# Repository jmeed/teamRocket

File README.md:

teamRocket
==========

Team Rocket Blasting off again!

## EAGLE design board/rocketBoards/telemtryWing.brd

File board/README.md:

Get Eagle 6.6 (not 7.1)

windows:
http://web.cadsoft.de/ftp/eagle/program/6.6/eagle-win-6.6.0.exe

linux:
http://web.cadsoft.de/ftp/eagle/program/6.6/eagle-lin-6.6.0.run

mac:
http://web.cadsoft.de/ftp/eagle/program/6.6/eagle-mac-6.6.0.zip

License Key for eagle 6.*: ficbbfxmxv

The license file is in this directory

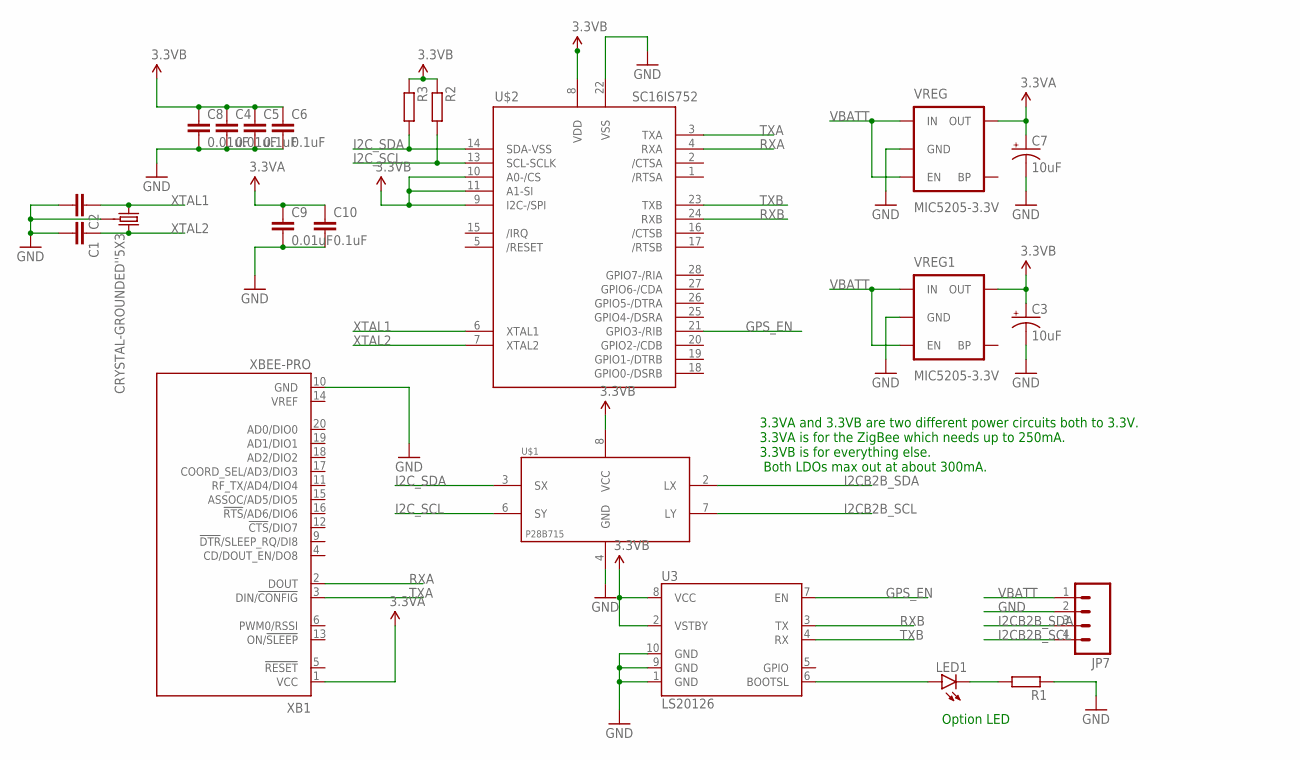
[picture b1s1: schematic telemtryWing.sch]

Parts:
C1, C2: C0603
C3, C7: 10uF; EIA3216
C4, C8, C9: 0.01uF; C0603
C5, C6, C10: 0.1uF; C0603
JP7: M04JST; 1X04-1.5MM_JST
LED1: LED0603; LED-0603
R1, R2, R3: R0603
U3: LS20126
U$1: P82B715; SO8
U$2: SC16IS752; TSSOP28
U$3: CRYSTAL-GROUNDED''5X3; CRYSTAL-SMD-5X3
VREG, VREG1: MIC5205-3.3V; SOT23-5
XB1: XBEE-PRO

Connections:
3.3V: C3.A (+), C4.1, C5.1, C6.1, C8.1, R2.1, R3.1, U3.2 (VSTBY), U3.8 (VCC), U$1.8 (VCC), U$2.8 (VDD), U$2.9 (I2C-/SPI), U$2.10 (A0-/CS), U$2.11 (A1-SI), VREG1.5 (OUT)
GND: C1.2, C2.2, C3.C (-), C4.2, C5.2, C6.2, C7.C (-), C8.2, C9.2, C10.2, JP7.2, R1.1, U3.1 (GND), U3.9 (GND), U3.10 (GND), U$1.4 (GND), U$2.22 (VSS), U$3.2 (3), U$3.4 (3), VREG.2 (GND), VREG1.2 (GND), XB1.10 (GND)
GPS_EN: U3.7 (EN), U$2.21 (GPIO3-/RIB)
I2CB2B_SCL: JP7.4, U$1.7 (LY)
I2CB2B_SDA: JP7.3, U$1.2 (LX)
I2C_SCL: R2.2, U$1.6 (SY), U$2.13 (SCL-SCLK)
I2C_SDA: R3.2, U$1.3 (SX), U$2.14 (SDA-VSS)
unnamed: LED1.C, R1.2
unnamed: LED1.A, U3.6 (BOOTSL)
RXA: U$2.4 (RXA), XB1.2 (DOUT)
RXB: U3.3 (TX), U$2.24 (RXB)
TXA: U$2.3 (TXA), XB1.3 (DIN/!CONFIG)
TXB: U3.4 (RX), U$2.23 (TXB)
VBATT: JP7.1, VREG.1 (IN), VREG.3 (EN), VREG1.1 (IN), VREG1.3 (EN)
VCC: C7.A (+), C9.1, C10.1, VREG.5 (OUT), XB1.1 (VCC)
XTAL1: C2.1, U$2.6 (XTAL1), U$3.3 (1)
XTAL2: C1.1, U$2.7 (XTAL2), U$3.1 (2)

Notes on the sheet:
3.3VA and 3.3VB are two different power circuits both to 3.3V. 3.3VA is for the ZigBee which needs up to 250mA. 3.3VB is for everything else. Both LDOs max out at about 300mA.
Option LED

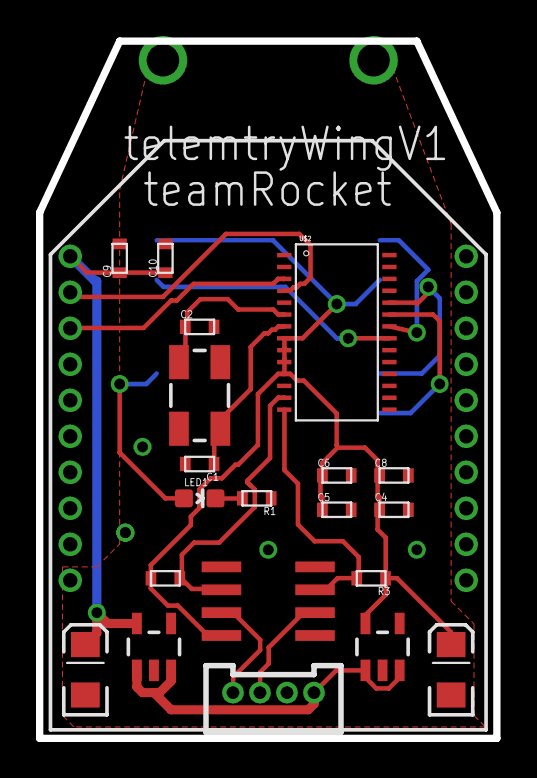
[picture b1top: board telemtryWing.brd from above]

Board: 2 copper layers, 25.4 x 38.7 mm, 22 parts (1 on the bottom side), 17 nets.

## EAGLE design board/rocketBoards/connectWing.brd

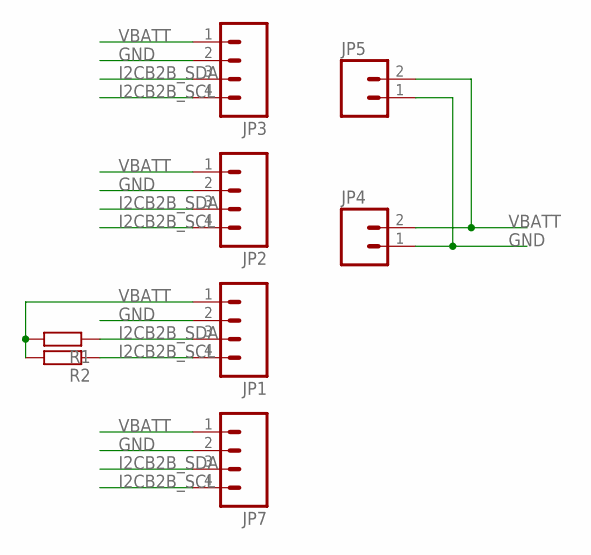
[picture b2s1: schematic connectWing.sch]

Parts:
JP1, JP2, JP3, JP7: M04JST; 1X04-1.5MM_JST
JP4, JP5: M021X02_NO_SILK; 1X02_NO_SILK
R1, R2: R0805

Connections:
GND: JP1.2, JP2.2, JP3.2, JP4.1, JP5.1, JP7.2
I2CB2B_SCL: JP1.4, JP2.4, JP3.4, JP7.4, R2.1
I2CB2B_SDA: JP1.3, JP2.3, JP3.3, JP7.3, R1.1
VBATT: JP1.1, JP2.1, JP3.1, JP4.2, JP5.2, JP7.1, R1.2, R2.2

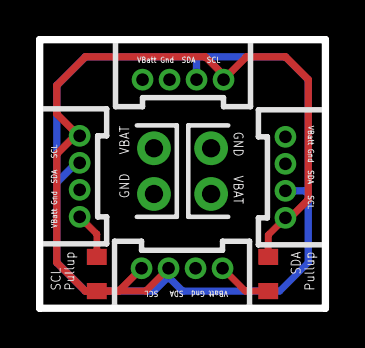
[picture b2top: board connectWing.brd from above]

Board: 2 copper layers, 15.9 x 14.9 mm, 8 parts (0 on the bottom side), 4 nets.

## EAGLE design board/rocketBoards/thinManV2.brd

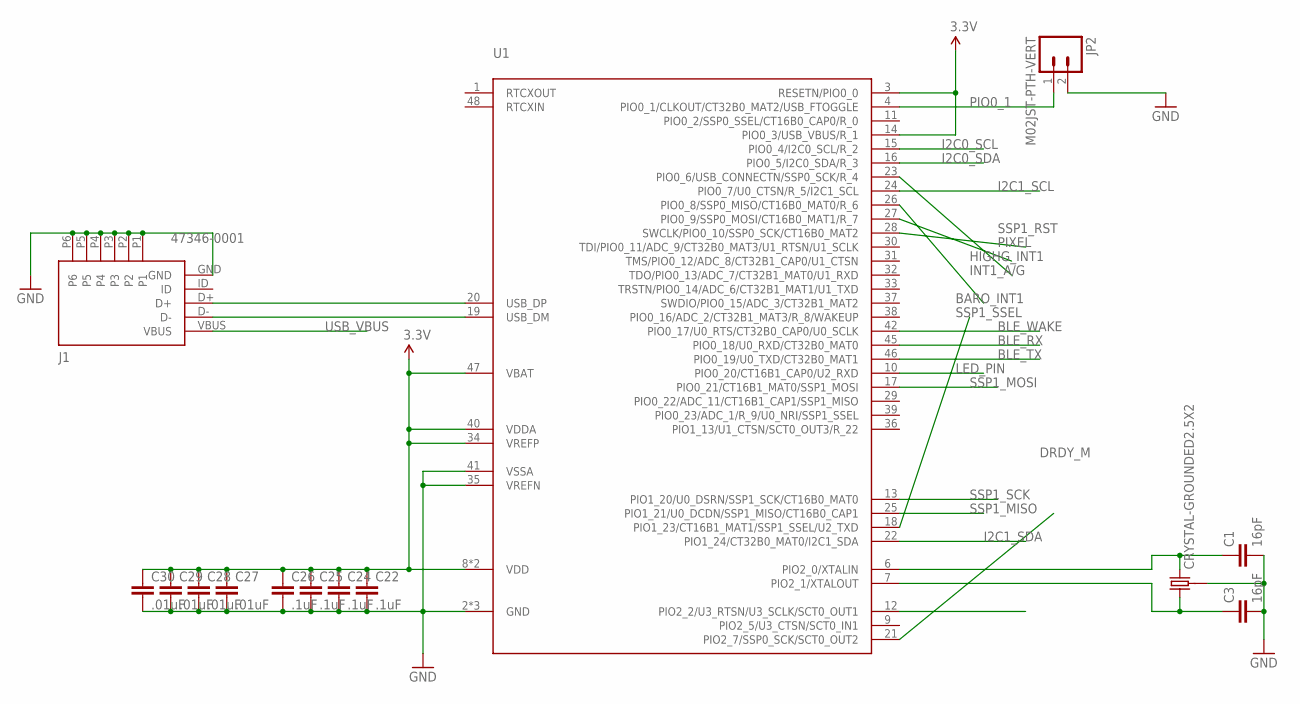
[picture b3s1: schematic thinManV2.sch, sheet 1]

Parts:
C1, C3: 16pF; C0603
C22, C24, C25, C26: .1uF; C0603
C27, C28, C29, C30: .01uF; C0603
J1: 47346-0001; MICRO_USB
JP2: M02JST-PTH-VERT; JST-2-PTH-VERT
U1: LPC11U68JBD48; LQFP48
U$5: CRYSTAL-GROUNDED2.5X2; CRYSTAL-SMD-2.5X2

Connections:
3.3V: C22.1, C24.1, C25.1, C26.1, C27.1, C28.1, C29.1, C30.1, U1.3 (RESETN/PIO0_0), U1.8 (VDD), U1.14 (PIO0_3/USB_VBUS/R_1), U1.34 (VREFP), U1.40 (VDDA), U1.44 (VDD), U1.47 (VBAT); also elsewhere on the board
BARO_INT1: U1.26 (PIO0_8/SSP0_MISO/CT16B0_MAT0/R_6); also elsewhere on the board
BLE_RX: U1.45 (PIO0_18/U0_RXD/CT32B0_MAT0); also elsewhere on the board
BLE_TX: U1.46 (PIO0_19/U0_TXD/CT32B0_MAT1); also elsewhere on the board
BLE_WAKE: U1.42 (PIO0_17/U0_RTS/CT32B0_CAP0/U0_SCLK); also elsewhere on the board
DRDY_M: U1.21 (PIO2_7/SSP0_SCK/SCT0_OUT2); also elsewhere on the board
GND: C1.2, C3.2, C22.2, C24.2, C25.2, C26.2, C27.2, C28.2, C29.2, C30.2, J1.GND, J1.P1, J1.P2, J1.P3, J1.P4, J1.P5, J1.P6, JP2.2, U1.2 (GND), U1.5 (GND), U1.35 (VREFN), U1.41 (VSSA), U1.43 (GND), U$5.GND1 (3), U$5.GND2 (3); also elsewhere on the board
HIGHG_INT1: U1.27 (PIO0_9/SSP0_MOSI/CT16B0_MAT1/R_7); also elsewhere on the board
I2C0_SCL: U1.15 (PIO0_4/I2C0_SCL/R_2); also elsewhere on the board
I2C0_SDA: U1.16 (PIO0_5/I2C0_SDA/R_3); also elsewhere on the board
I2C1_SCL: U1.24 (PIO0_7/U0_CTSN/R_5/I2C1_SCL); also elsewhere on the board
I2C1_SDA: U1.22 (PIO1_24/CT32B0_MAT0/I2C1_SDA); also elsewhere on the board
INT1_A/G: U1.23 (PIO0_6/USB_CONNECTN/SSP0_SCK/R_4); also elsewhere on the board
LED_PIN: U1.10 (PIO0_20/CT16B1_CAP0/U2_RXD); also elsewhere on the board
unnamed: C3.1, U1.7 (PIO2_1/XTALOUT), U$5.P1 (1)
unnamed: C1.1, U1.6 (PIO2_0/XTALIN), U$5.P2 (2)
unnamed: J1.D+, U1.20 (USB_DP)
unnamed: J1.D-, U1.19 (USB_DM)
PIO0_1: JP2.1, U1.4 (PIO0_1/CLKOUT/CT32B0_MAT2/USB_FTOGGLE)
PIXEL: U1.28 (SWCLK/PIO0_10/SSP0_SCK/CT16B0_MAT2); also elsewhere on the board
SSP1_MISO: U1.25 (PIO1_21/U0_DCDN/SSP1_MISO/CT16B0_CAP1); also elsewhere on the board
SSP1_MOSI: U1.17 (PIO0_21/CT16B1_MAT0/SSP1_MOSI); also elsewhere on the board
SSP1_RST: U1.12 (PIO2_2/U3_RTSN/U3_SCLK/SCT0_OUT1); also elsewhere on the board
SSP1_SCK: U1.13 (PIO1_20/U0_DSRN/SSP1_SCK/CT16B0_MAT0); also elsewhere on the board
SSP1_SSEL: U1.18 (PIO1_23/CT16B1_MAT1/SSP1_SSEL/U2_TXD); also elsewhere on the board
USB_VBUS: J1.VBUS; also elsewhere on the board

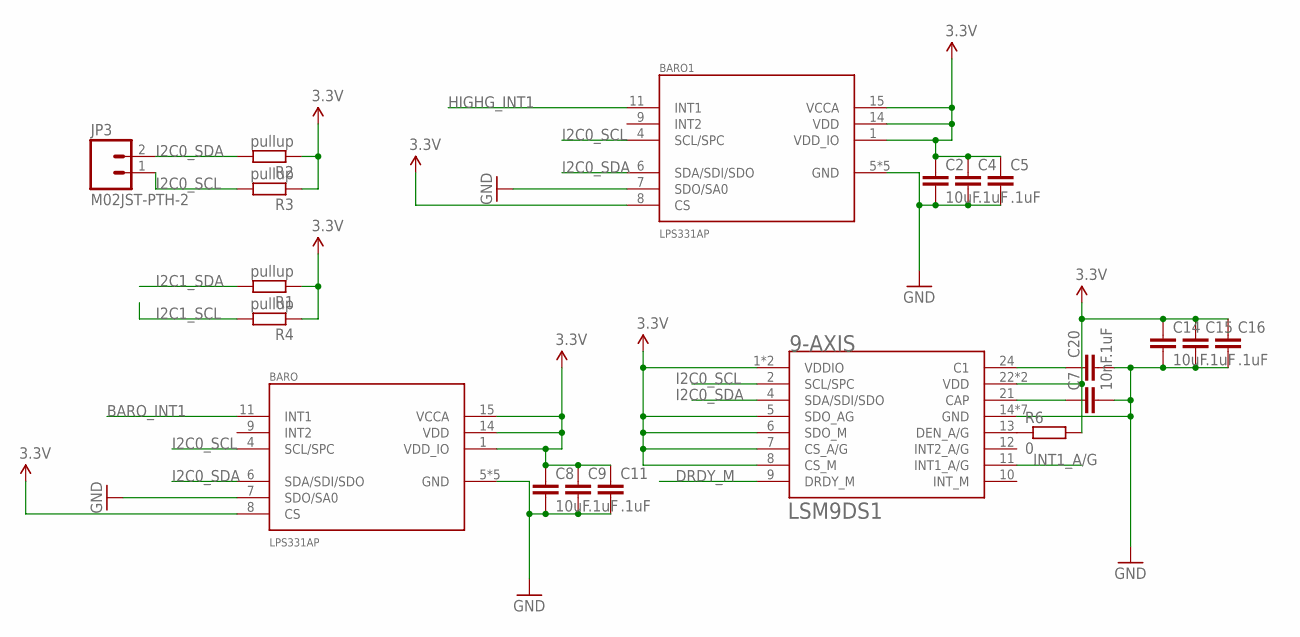
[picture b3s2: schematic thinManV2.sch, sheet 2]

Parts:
9-AXIS: LSM9DS1; LGA-24L-3.5X3X1
BARO, BARO1: LPS331AP; LGA-16-3X3X1; MPN LPS331APTR
C2, C8, C14: 10uF; C0603
C4, C5, C9, C11, C15, C16: .1uF; C0603
C7: 10nF; C0603; MPN S103M47Z5UN63L0R
C20: .1uF; C0603; MPN S103M47Z5UN63L0R
JP3: M02JST-PTH-2; JST-2-PTH
R1, R4: pullup; R0805
R2, R3: pullup; R0603
R6: 0; R0603

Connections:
3.3V: 9-AXIS.1 (VDDIO), 9-AXIS.3 (VDDIO), 9-AXIS.5 (SDO_AG), 9-AXIS.6 (SDO_M), 9-AXIS.7 (CS_A/G), 9-AXIS.8 (CS_M), 9-AXIS.22 (VDD), 9-AXIS.23 (VDD), BARO.1 (VDD_IO), BARO.8 (CS), BARO.14 (VDD), BARO.15 (VCCA), BARO1.1 (VDD_IO), BARO1.8 (CS), BARO1.14 (VDD), BARO1.15 (VCCA), C2.1, C4.1, C5.1, C8.1, C9.1, C11.1, C14.1, C15.1, C16.1, R1.1, R2.1, R3.1, R4.1, R6.2; also elsewhere on the board
BARO_INT1: BARO.11 (INT1); also elsewhere on the board
DRDY_M: 9-AXIS.9 (DRDY_M); also elsewhere on the board
GND: 9-AXIS.14 (GND), 9-AXIS.15 (GND), 9-AXIS.16 (GND), 9-AXIS.17 (GND), 9-AXIS.18 (GND), 9-AXIS.19 (GND), 9-AXIS.20 (GND), BARO.5 (GND), BARO.7 (SDO/SA0), BARO.10 (GND), BARO.12 (GND), BARO.13 (GND), BARO.16 (GND), BARO1.5 (GND), BARO1.7 (SDO/SA0), BARO1.10 (GND), BARO1.12 (GND), BARO1.13 (GND), BARO1.16 (GND), C2.2, C4.2, C5.2, C7.2, C8.2, C9.2, C11.2, C14.2, C15.2, C16.2, C20.2; also elsewhere on the board
HIGHG_INT1: BARO1.11 (INT1); also elsewhere on the board
I2C0_SCL: 9-AXIS.2 (SCL/SPC), BARO.4 (SCL/SPC), BARO1.4 (SCL/SPC), JP3.1, R3.2; also elsewhere on the board
I2C0_SDA: 9-AXIS.4 (SDA/SDI/SDO), BARO.6 (SDA/SDI/SDO), BARO1.6 (SDA/SDI/SDO), JP3.2, R2.2; also elsewhere on the board
I2C1_SCL: R4.2; also elsewhere on the board
I2C1_SDA: R1.2; also elsewhere on the board
INT1_A/G: 9-AXIS.11 (INT1_A/G); also elsewhere on the board
unnamed: 9-AXIS.13 (DEN_A/G), R6.1
unnamed: 9-AXIS.21 (CAP), C7.1
unnamed: 9-AXIS.24 (C1), C20.1

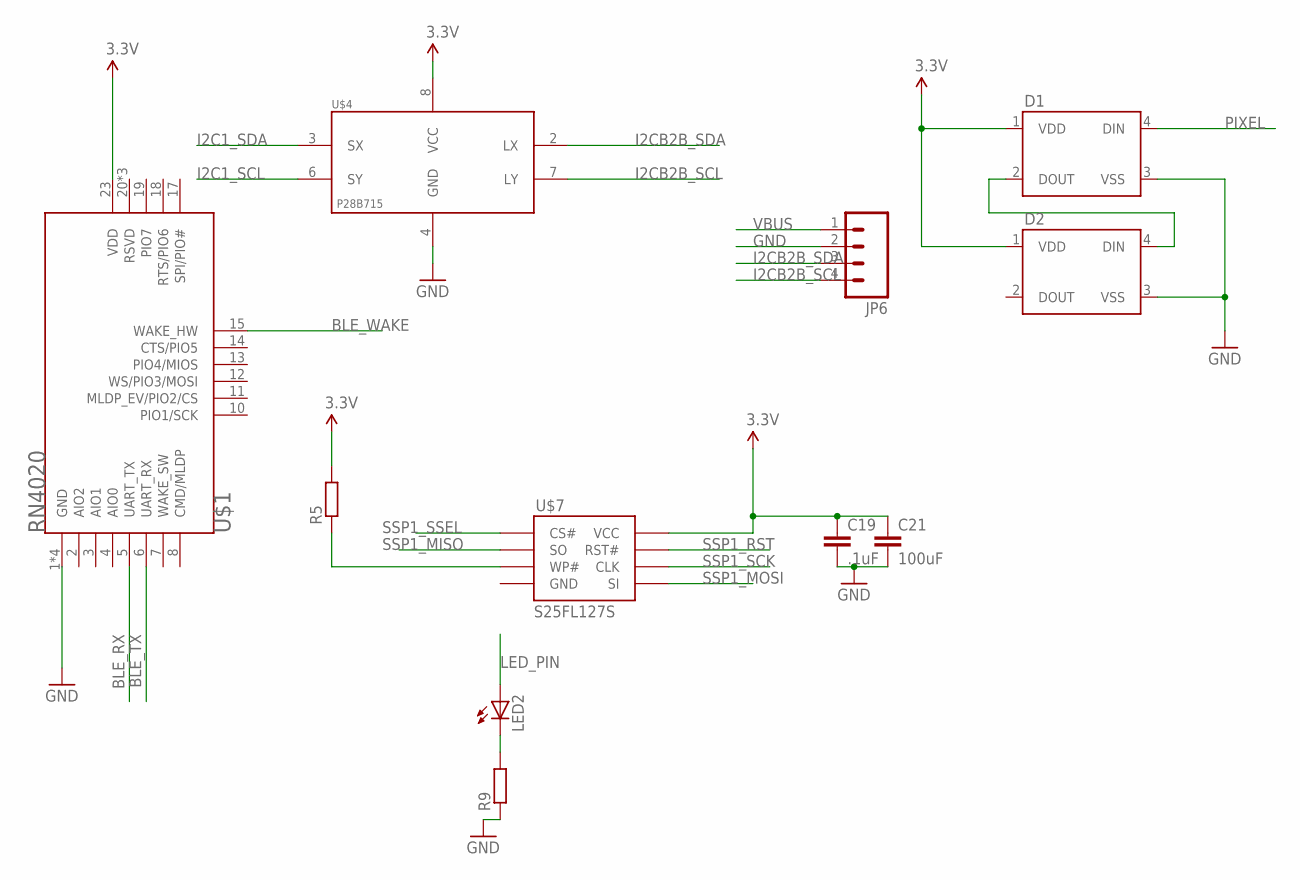
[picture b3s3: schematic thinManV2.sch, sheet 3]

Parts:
C19: .1uF; C0603
C21: 100uF; C0603
D1, D2: WS2812B
JP6: M04JST; 1X04-1.5MM_JST
LED2: LEDCHIPLED_0603; CHIPLED_0603
R5, R9: R0603
U$1: RN4020
U$4: P82B715; SO8
U$7: S25FL127S; SO08

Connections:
3.3V: C19.1, C21.1, D1.1 (VDD), D2.1 (VDD), R5.2, U$1.23 (VDD), U$4.8 (VCC), U$7.8 (VCC); also elsewhere on the board
BLE_RX: U$1.5 (UART_TX); also elsewhere on the board
BLE_TX: U$1.6 (UART_RX); also elsewhere on the board
BLE_WAKE: U$1.15 (WAKE_HW); also elsewhere on the board
GND: C19.2, C21.2, D1.3 (VSS), D2.3 (VSS), JP6.2, R9.1, U$1.1 (GND), U$1.9 (GND), U$1.16 (GND), U$1.24 (GND), U$4.4 (GND); also elsewhere on the board
I2C1_SCL: U$4.6 (SY); also elsewhere on the board
I2C1_SDA: U$4.3 (SX); also elsewhere on the board
I2CB2B_SCL: JP6.4, U$4.7 (LY)
I2CB2B_SDA: JP6.3, U$4.2 (LX)
LED_PIN: LED2.A; also elsewhere on the board
unnamed: R5.1, U$7.3 (WP#)
unnamed: LED2.C, R9.2
unnamed: D1.2 (DOUT), D2.4 (DIN)
PIXEL: D1.4 (DIN); also elsewhere on the board
SSP1_MISO: U$7.2 (SO); also elsewhere on the board
SSP1_MOSI: U$7.5 (SI); also elsewhere on the board
SSP1_RST: U$7.7 (RST#); also elsewhere on the board
SSP1_SCK: U$7.6 (CLK); also elsewhere on the board
SSP1_SSEL: U$7.1 (CS#); also elsewhere on the board
VBUS: JP6.1; also elsewhere on the board

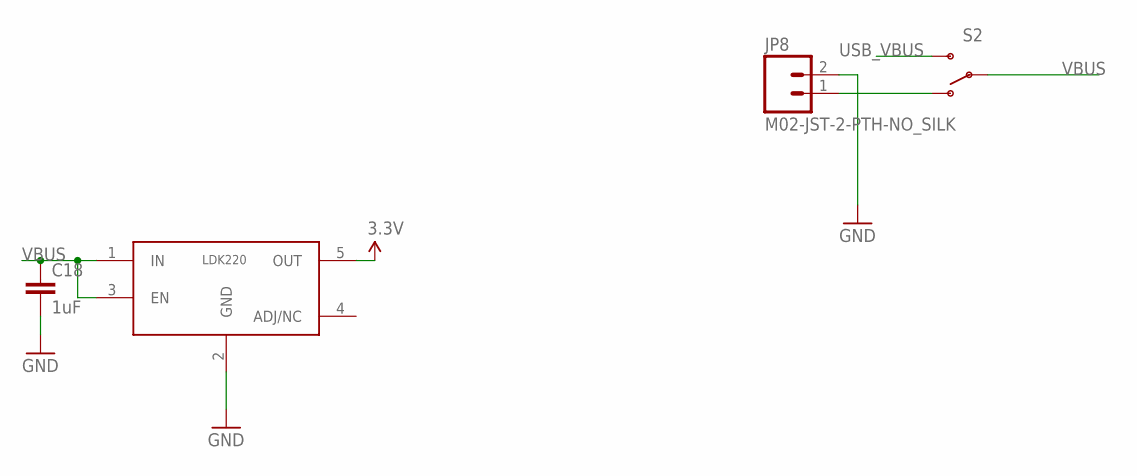
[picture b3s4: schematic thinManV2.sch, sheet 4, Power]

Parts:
C18: 1uF; C0603
JP8: M02-JST-2-PTH-NO_SILK; JST-2-PTH-NS
S2: SWITCH-SPDT-SMD-A; SWITCH-SPST-SMD-A
U$6: LDK220M33R; SOT23-5

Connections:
3.3V: U$6.5 (OUT); also elsewhere on the board
GND: C18.2, JP8.2, U$6.2 (GND); also elsewhere on the board
unnamed: JP8.1, S2.1 (O)
USB_VBUS: S2.3 (S); also elsewhere on the board
VBUS: C18.1, S2.2, U$6.1 (IN), U$6.3 (EN); also elsewhere on the board

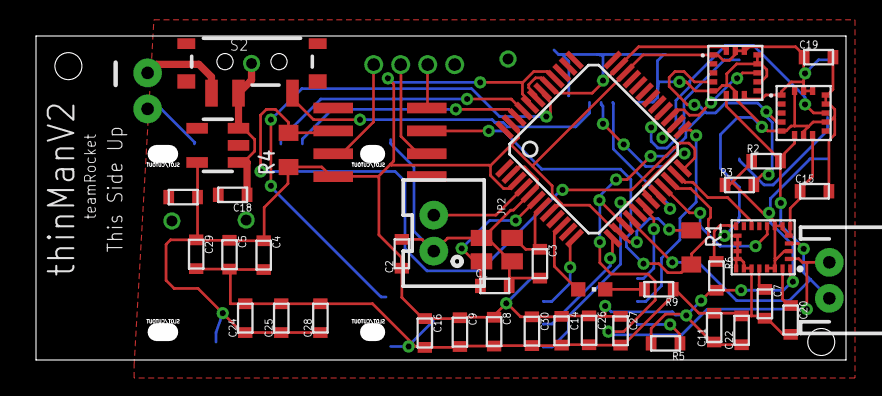
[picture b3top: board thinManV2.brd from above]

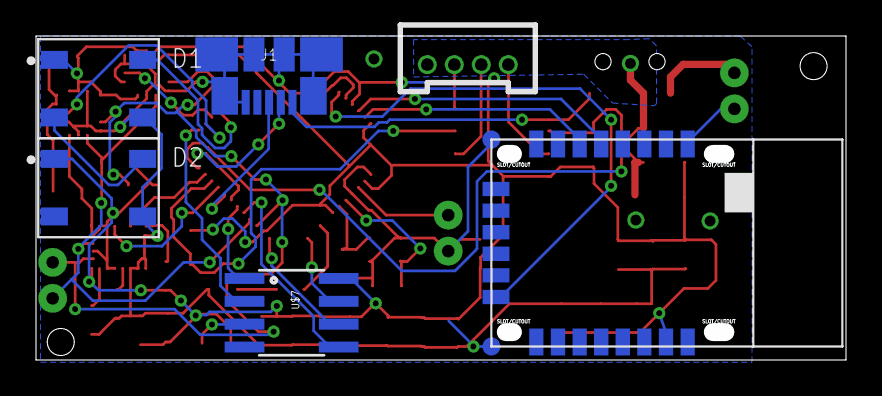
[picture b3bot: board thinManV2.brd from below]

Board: 2 copper layers, 45.0 x 18.0 mm, 49 parts (7 on the bottom side), 36 nets.

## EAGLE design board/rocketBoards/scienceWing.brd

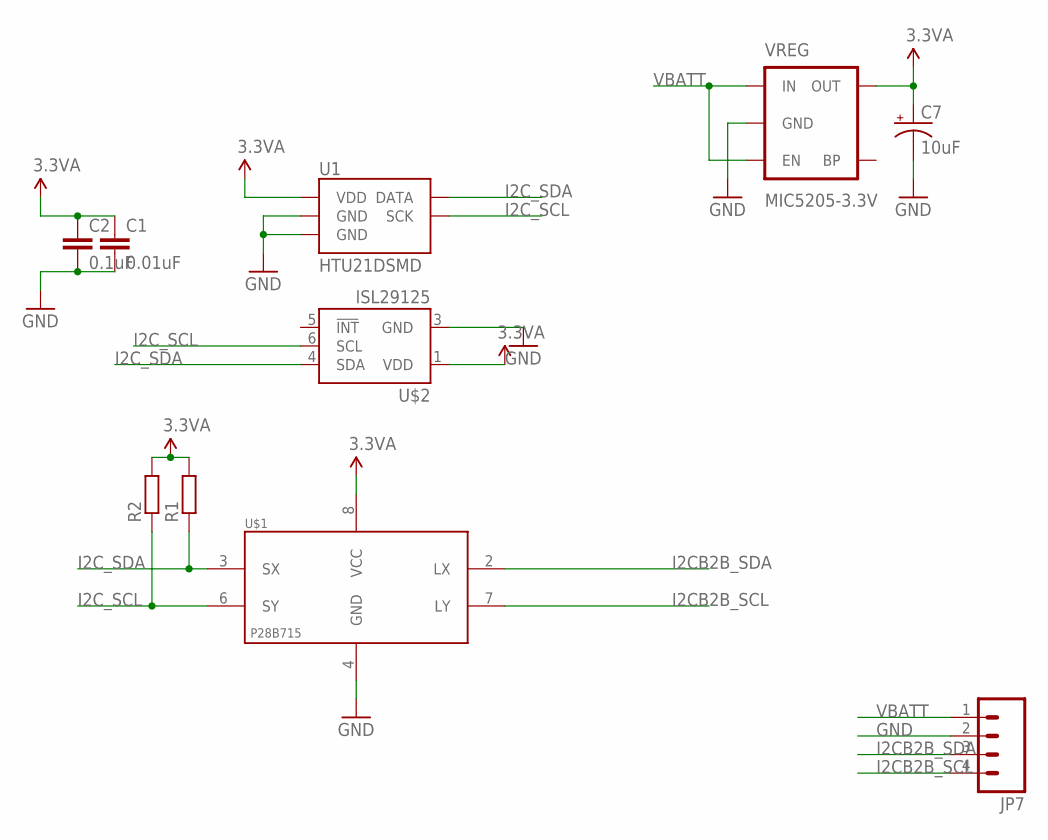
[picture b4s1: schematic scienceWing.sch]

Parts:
C1: 0.01uF; C0603
C2: 0.1uF; C0603
C7: 10uF; EIA3216
JP7: M04JST; 1X04-1.5MM_JST
R1, R2: R0603
U1: HTU21DSMD; HTU21D
U$1: P82B715; SO8
U$2: ISL29125; ODFN-LD-6
VREG: MIC5205-3.3V; SOT23-5

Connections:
GND: C1.2, C2.2, C7.C (-), JP7.2, U1.7 (GND), U1.GND, U$1.4 (GND), U$2.3 (GND), VREG.2 (GND)
I2CB2B_SCL: JP7.4, U$1.7 (LY)
I2CB2B_SDA: JP7.3, U$1.2 (LX)
I2C_SCL: R2.1, U1.SCK, U$1.6 (SY), U$2.6 (SCL)
I2C_SDA: R1.1, U1.DATA, U$1.3 (SX), U$2.4 (SDA)
VBATT: JP7.1, VREG.1 (IN), VREG.3 (EN)
VCC: C1.1, C2.1, C7.A (+), R1.2, R2.2, U1.VDD, U$1.8 (VCC), U$2.1 (VDD), VREG.5 (OUT)

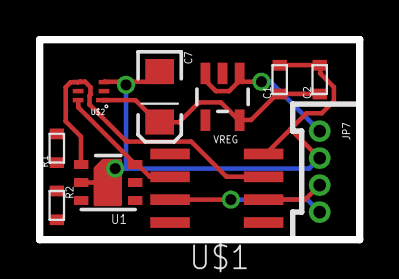
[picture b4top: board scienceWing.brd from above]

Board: 2 copper layers, 17.8 x 11.1 mm, 10 parts (0 on the bottom side), 7 nets.

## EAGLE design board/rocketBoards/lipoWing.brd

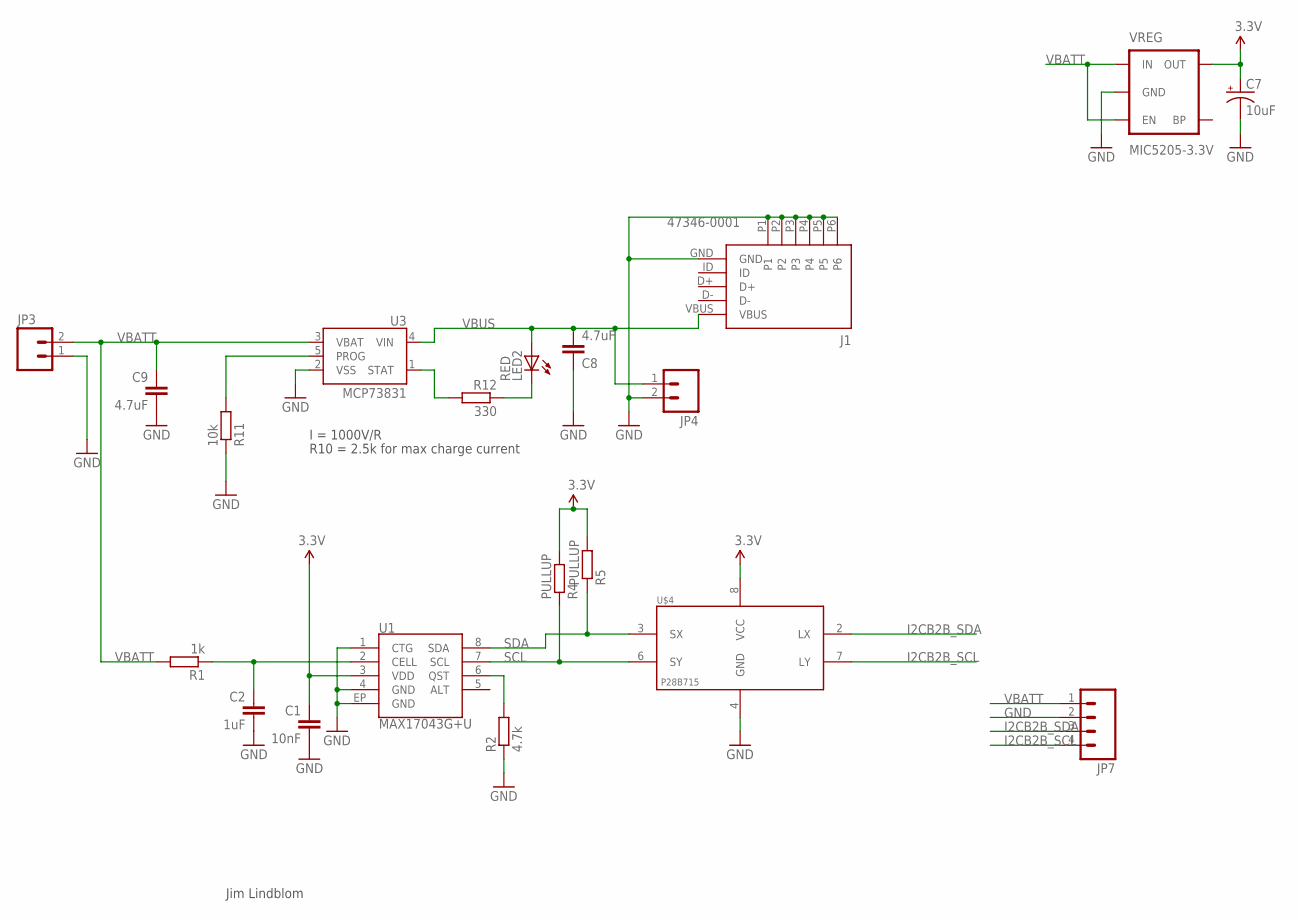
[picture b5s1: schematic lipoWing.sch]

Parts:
C1: 10nF; C0603
C2: 1uF; C0603
C7: 10uF; EIA3216
C8, C9: 4.7uF; C0603
J1: 47346-0001; MICRO_USB
JP3, JP4: M021X02_NO_SILK; 1X02_NO_SILK
JP7: M04JST; 1X04-1.5MM_JST
LED2: RED; LED-0603
R1: 1k; R0603
R2: 4.7k; R0603
R4, R5: PULLUP; R0603
R11: 10k; R0603
R12: 330; R0603
U1: MAX17043G+U; TDFN-8
U3: MCP73831; SOT23-5
U$4: P82B715; SO8
VREG: MIC5205-3.3V; SOT23-5

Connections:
3.3V: C1.1, C7.A (+), R4.2, R5.2, U1.3 (VDD), U$4.8 (VCC), VREG.5 (OUT)
CELL: C2.1, R1.1, U1.2 (CELL)
GND: C1.2, C2.2, C7.C (-), C8.1, C9.2, J1.GND, J1.P1, J1.P2, J1.P3, J1.P4, J1.P5, J1.P6, JP3.1, JP4.2, JP7.2, R2.1, R11.1, U1.1 (CTG), U1.4 (GND), U1.EP (GND), U3.2 (VSS), U$4.4 (GND), VREG.2 (GND)
I2CB2B_SCL: JP7.4, U$4.7 (LY)
I2CB2B_SDA: JP7.3, U$4.2 (LX)
unnamed: LED2.C, R12.1
PROG: R11.2, U3.5 (PROG)
QST: R2.2, U1.6 (QST)
SCL: R4.1, U1.7 (SCL), U$4.6 (SY)
SDA: R5.1, U1.8 (SDA), U$4.3 (SX)
STAT: R12.2, U3.1 (STAT)
VBATT: C9.1, JP3.2, JP7.1, R1.2, U3.3 (VBAT), VREG.1 (IN), VREG.3 (EN)
VBUS: C8.2, J1.VBUS, JP4.1, LED2.A, U3.4 (VIN)

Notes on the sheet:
Jim Lindblom
I = 1000V/R
R10 = 2.5k for max charge current

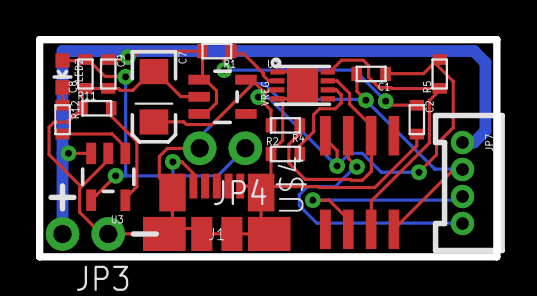
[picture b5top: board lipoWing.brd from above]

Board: 2 copper layers, 25.4 x 12.1 mm, 20 parts (0 on the bottom side), 13 nets.

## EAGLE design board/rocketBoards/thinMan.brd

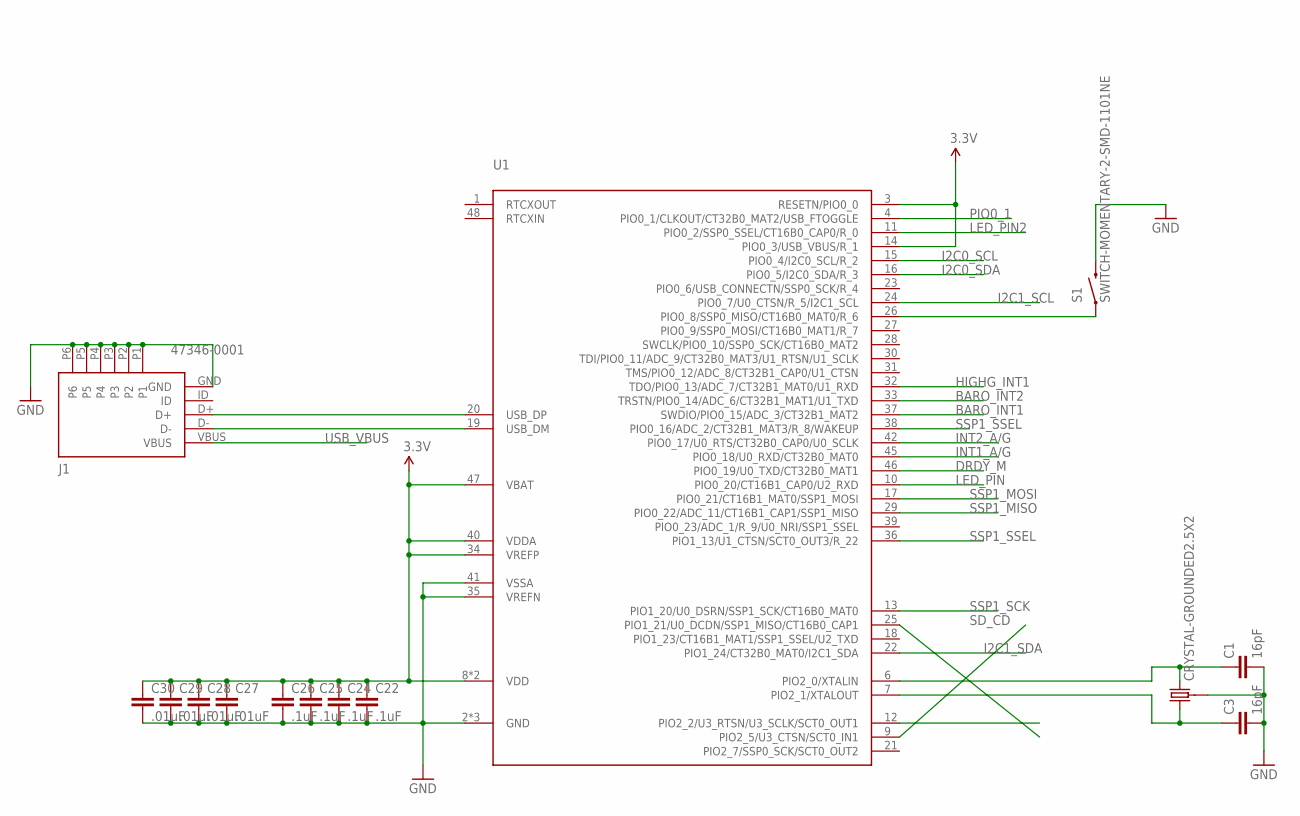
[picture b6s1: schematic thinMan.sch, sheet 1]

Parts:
C1, C3: 16pF; C0402
C22, C24, C25, C26: .1uF; C0402
C27, C28, C29, C30: .01uF; C0402
J1: 47346-0001; MICRO_USB
S1: SWITCH-MOMENTARY-2-SMD-1101NE; TACTILE-SWITCH-1101NE
U1: LPC11U68JBD48; LQFP48
U$5: CRYSTAL-GROUNDED2.5X2; CRYSTAL-SMD-2.5X2

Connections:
3.3V: C22.1, C24.1, C25.1, C26.1, C27.1, C28.1, C29.1, C30.1, U1.3 (RESETN/PIO0_0), U1.8 (VDD), U1.14 (PIO0_3/USB_VBUS/R_1), U1.34 (VREFP), U1.40 (VDDA), U1.44 (VDD), U1.47 (VBAT); also elsewhere on the board
BARO_INT1: U1.37 (SWDIO/PIO0_15/ADC_3/CT32B1_MAT2); also elsewhere on the board
BARO_INT2: U1.33 (TRSTN/PIO0_14/ADC_6/CT32B1_MAT1/U1_TXD)
DRDY_M: U1.46 (PIO0_19/U0_TXD/CT32B0_MAT1); also elsewhere on the board
GND: C1.2, C3.2, C22.2, C24.2, C25.2, C26.2, C27.2, C28.2, C29.2, C30.2, J1.GND, J1.P1, J1.P2, J1.P3, J1.P4, J1.P5, J1.P6, S1.2, U1.2 (GND), U1.5 (GND), U1.35 (VREFN), U1.41 (VSSA), U1.43 (GND), U$5.GND1 (3), U$5.GND2 (3); also elsewhere on the board
HIGHG_INT1: U1.32 (TDO/PIO0_13/ADC_7/CT32B1_MAT0/U1_RXD)
HIGHG_INT2: U1.36 (PIO1_13/U1_CTSN/SCT0_OUT3/R_22)
I2C0_SCL: U1.15 (PIO0_4/I2C0_SCL/R_2); also elsewhere on the board
I2C0_SDA: U1.16 (PIO0_5/I2C0_SDA/R_3); also elsewhere on the board
I2C1_SCL: U1.24 (PIO0_7/U0_CTSN/R_5/I2C1_SCL); also elsewhere on the board
I2C1_SDA: U1.22 (PIO1_24/CT32B0_MAT0/I2C1_SDA); also elsewhere on the board
INT1_A/G: U1.45 (PIO0_18/U0_RXD/CT32B0_MAT0); also elsewhere on the board
INT2_A/G: U1.42 (PIO0_17/U0_RTS/CT32B0_CAP0/U0_SCLK)
LED_PIN: U1.10 (PIO0_20/CT16B1_CAP0/U2_RXD); also elsewhere on the board
LED_PIN2: U1.11 (PIO0_2/SSP0_SSEL/CT16B0_CAP0/R_0); also elsewhere on the board
unnamed: C3.1, U1.7 (PIO2_1/XTALOUT), U$5.P1 (1)
unnamed: C1.1, U1.6 (PIO2_0/XTALIN), U$5.P2 (2)
unnamed: J1.D+, U1.20 (USB_DP)
unnamed: J1.D-, U1.19 (USB_DM)
unnamed: S1.1, U1.26 (PIO0_8/SSP0_MISO/CT16B0_MAT0/R_6)
PIO0_1: U1.4 (PIO0_1/CLKOUT/CT32B0_MAT2/USB_FTOGGLE); also elsewhere on the board
SD_CD: U1.9 (PIO2_5/U3_CTSN/SCT0_IN1); also elsewhere on the board
SSP1_MISO: U1.29 (PIO0_22/ADC_11/CT16B1_CAP1/SSP1_MISO); also elsewhere on the board
SSP1_MOSI: U1.17 (PIO0_21/CT16B1_MAT0/SSP1_MOSI); also elsewhere on the board
SSP1_SCK: U1.13 (PIO1_20/U0_DSRN/SSP1_SCK/CT16B0_MAT0); also elsewhere on the board
SSP1_SSEL: U1.38 (PIO0_16/ADC_2/CT32B1_MAT3/R_8/WAKEUP); also elsewhere on the board
USB_VBUS: J1.VBUS; also elsewhere on the board

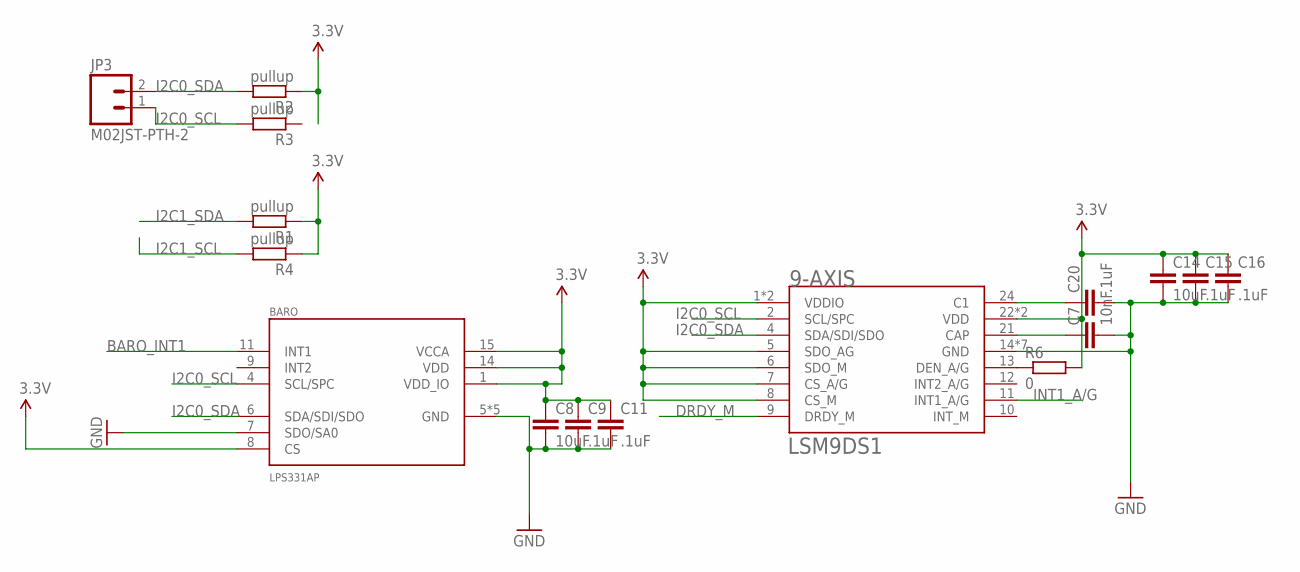
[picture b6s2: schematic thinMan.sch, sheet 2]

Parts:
9-AXIS: LSM9DS1; LGA-24L-3.5X3X1
BARO: LPS331AP; LGA-16-3X3X1; MPN LPS331APTR
C7: 10nF; C0402; MPN S103M47Z5UN63L0R
C8, C14: 10uF; C0402
C9, C11, C15, C16: .1uF; C0402
C20: .1uF; C0402; MPN S103M47Z5UN63L0R
JP3: M02JST-PTH-2; JST-2-PTH
R1, R4: pullup; R0805
R2, R3: pullup; R0402
R6: 0; R0402

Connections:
3.3V: 9-AXIS.1 (VDDIO), 9-AXIS.3 (VDDIO), 9-AXIS.5 (SDO_AG), 9-AXIS.6 (SDO_M), 9-AXIS.7 (CS_A/G), 9-AXIS.8 (CS_M), 9-AXIS.22 (VDD), 9-AXIS.23 (VDD), BARO.1 (VDD_IO), BARO.8 (CS), BARO.14 (VDD), BARO.15 (VCCA), C8.1, C9.1, C11.1, C14.1, C15.1, C16.1, R1.1, R2.1, R4.1, R6.2; also elsewhere on the board
BARO_INT1: BARO.11 (INT1); also elsewhere on the board
DRDY_M: 9-AXIS.9 (DRDY_M); also elsewhere on the board
GND: 9-AXIS.14 (GND), 9-AXIS.15 (GND), 9-AXIS.16 (GND), 9-AXIS.17 (GND), 9-AXIS.18 (GND), 9-AXIS.19 (GND), 9-AXIS.20 (GND), BARO.5 (GND), BARO.7 (SDO/SA0), BARO.10 (GND), BARO.12 (GND), BARO.13 (GND), BARO.16 (GND), C7.2, C8.2, C9.2, C11.2, C14.2, C15.2, C16.2, C20.2; also elsewhere on the board
I2C0_SCL: 9-AXIS.2 (SCL/SPC), BARO.4 (SCL/SPC), JP3.1, R3.2; also elsewhere on the board
I2C0_SDA: 9-AXIS.4 (SDA/SDI/SDO), BARO.6 (SDA/SDI/SDO), JP3.2, R2.2; also elsewhere on the board
I2C1_SCL: R4.2; also elsewhere on the board
I2C1_SDA: R1.2; also elsewhere on the board
INT1_A/G: 9-AXIS.11 (INT1_A/G); also elsewhere on the board
unnamed: 9-AXIS.13 (DEN_A/G), R6.1
unnamed: 9-AXIS.21 (CAP), C7.1
unnamed: 9-AXIS.24 (C1), C20.1

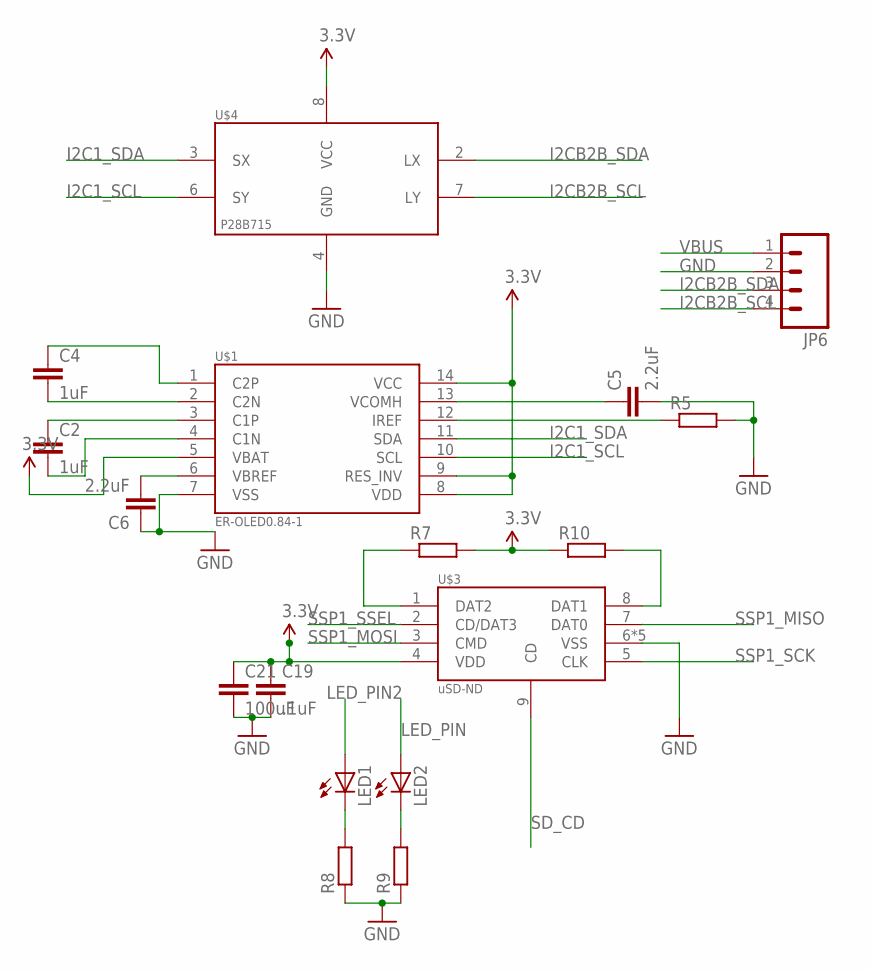
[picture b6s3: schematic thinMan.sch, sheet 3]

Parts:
C2, C4: 1uF; C0402; MPN MC0402X105M6R3CT
C5, C6: 2.2uF; C0402; MPN C1005X6S0G225M050BC
C19: .1uF; C0402
C21: 100uF; C1206
JP6: M04JST; 1X04-1.5MM_JST
LED1, LED2: LEDCHIPLED_0603; CHIPLED_0603
R5, R7, R8, R9, R10: R0402
U$1: ER-OLED0.84-1; MOLEX_52892-1433
U$3: MICROSD-CD; MOLEX_SD-47352-101
U$4: P82B715; SO8

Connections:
3.3V: C19.1, C21.1, R7.2, R10.1, U$1.5 (VBAT), U$1.8 (VDD), U$1.9 (RES_INV), U$1.14 (VCC), U$3.4 (VDD), U$4.8 (VCC); also elsewhere on the board
GND: C5.2, C6.1, C19.2, C21.2, JP6.2, R5.2, R8.1, R9.1, U$1.7 (VSS), U$3.6 (VSS), U$3.G1 (VSS), U$3.G2 (VSS), U$3.G3 (VSS), U$3.G4 (VSS), U$4.4 (GND); also elsewhere on the board
I2C1_SCL: U$1.10 (SCL), U$4.6 (SY); also elsewhere on the board
I2C1_SDA: U$1.11 (SDA), U$4.3 (SX); also elsewhere on the board
I2CB2B_SCL: JP6.4, U$4.7 (LY)
I2CB2B_SDA: JP6.3, U$4.2 (LX)
LED_PIN: LED2.A; also elsewhere on the board
LED_PIN2: LED1.A; also elsewhere on the board
unnamed: LED1.C, R8.2
unnamed: LED2.C, R9.2
unnamed: C4.1, U$1.1 (C2P)
unnamed: C4.2, U$1.2 (C2N)
unnamed: C2.1, U$1.3 (C1P)
unnamed: C2.2, U$1.4 (C1N)
unnamed: C5.1, U$1.13 (VCOMH)
unnamed: R5.1, U$1.12 (IREF)
unnamed: C6.2, U$1.6 (VBREF)
unnamed: R7.1, U$3.1 (DAT2)
unnamed: R10.2, U$3.8 (DAT1)
SD_CD: U$3.9 (CD); also elsewhere on the board
SSP1_MISO: U$3.7 (DAT0); also elsewhere on the board
SSP1_MOSI: U$3.3 (CMD); also elsewhere on the board
SSP1_SCK: U$3.5 (CLK); also elsewhere on the board
SSP1_SSEL: U$3.2 (CD/DAT3); also elsewhere on the board
VBUS: JP6.1; also elsewhere on the board

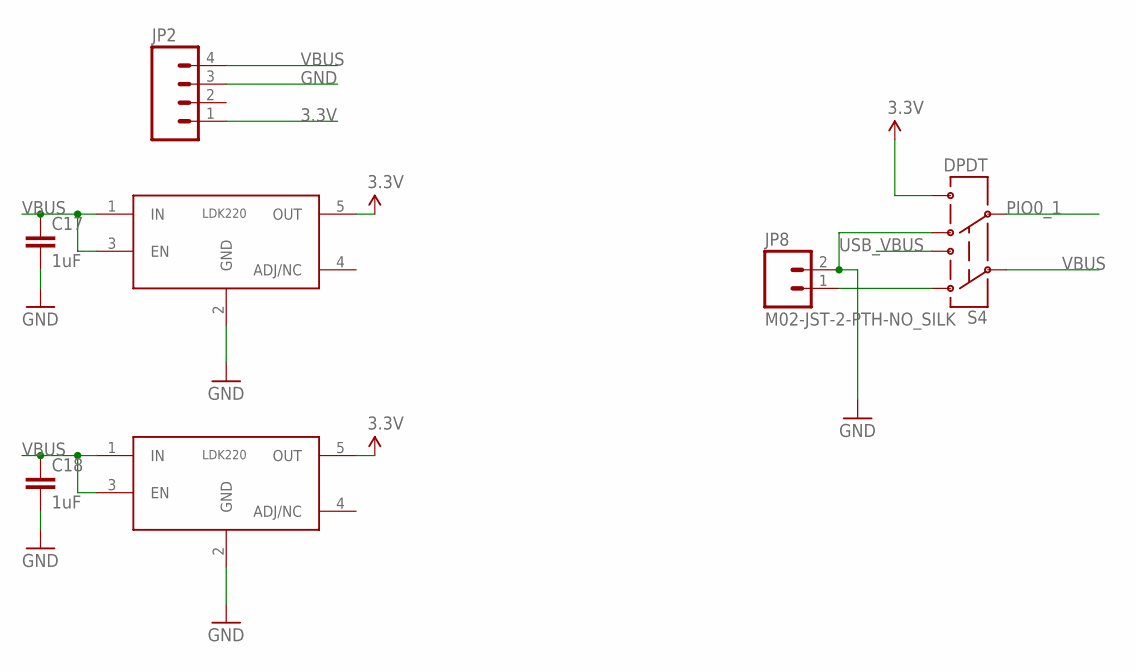
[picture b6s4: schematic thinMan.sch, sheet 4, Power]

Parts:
C17, C18: 1uF; C0402
JP2: M04JST; 1X04-1.5MM_JST
JP8: M02-JST-2-PTH-NO_SILK; JST-2-PTH-NS
S4: DPDT; AYZ0202
U$2, U$6: LDK220M33R; SOT23-5

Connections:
3.3V: JP2.1, S4.6, U$2.5 (OUT), U$6.5 (OUT); also elsewhere on the board
GND: C17.2, C18.2, JP2.3, JP8.2, S4.4, U$2.2 (GND), U$6.2 (GND); also elsewhere on the board
unnamed: JP8.1, S4.1
PIO0_1: S4.5; also elsewhere on the board
USB_VBUS: S4.3; also elsewhere on the board
VBUS: C17.1, C18.1, JP2.4, S4.2, U$2.1 (IN), U$2.3 (EN), U$6.1 (IN), U$6.3 (EN); also elsewhere on the board

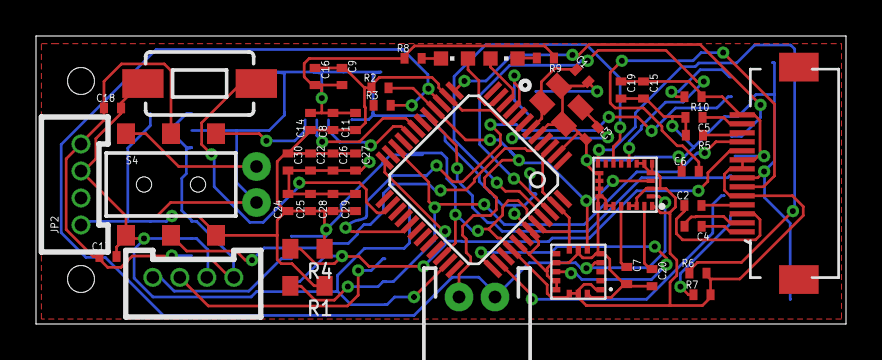
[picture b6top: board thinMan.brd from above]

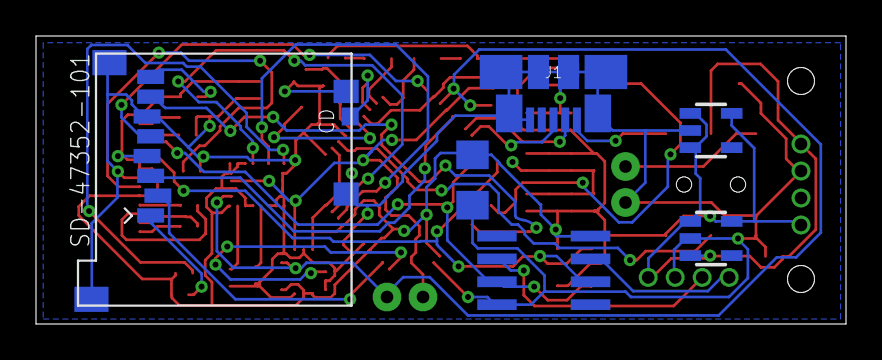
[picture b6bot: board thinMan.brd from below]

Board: 2 copper layers, 45.0 x 16.0 mm, 54 parts (7 on the bottom side), 41 nets.

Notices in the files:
src/sensor_test/lpc_board_nxp_lpcxpresso_11u68/src/board_sysinit.c:
Copyright(C) NXP Semiconductors, 2013
All rights reserved.
parts and their libraries:
SparkFun-Connectors: Licensing: Creative Commons ShareAlike 4.0 International - https://creativecommons.org/licenses/by-sa/4.0
ELL-i-Passives: Eagle package Copyright (c) SparkFun under Creative Commons v3.0 Share Alike license.
